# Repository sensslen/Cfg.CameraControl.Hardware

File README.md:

# Cfg.CameraControl.Hardware
Hardware needed to control a lanc camera with a PTZ head

The schematic looks like: 

## additional info
https://github.com/egnor/wt32-eth01

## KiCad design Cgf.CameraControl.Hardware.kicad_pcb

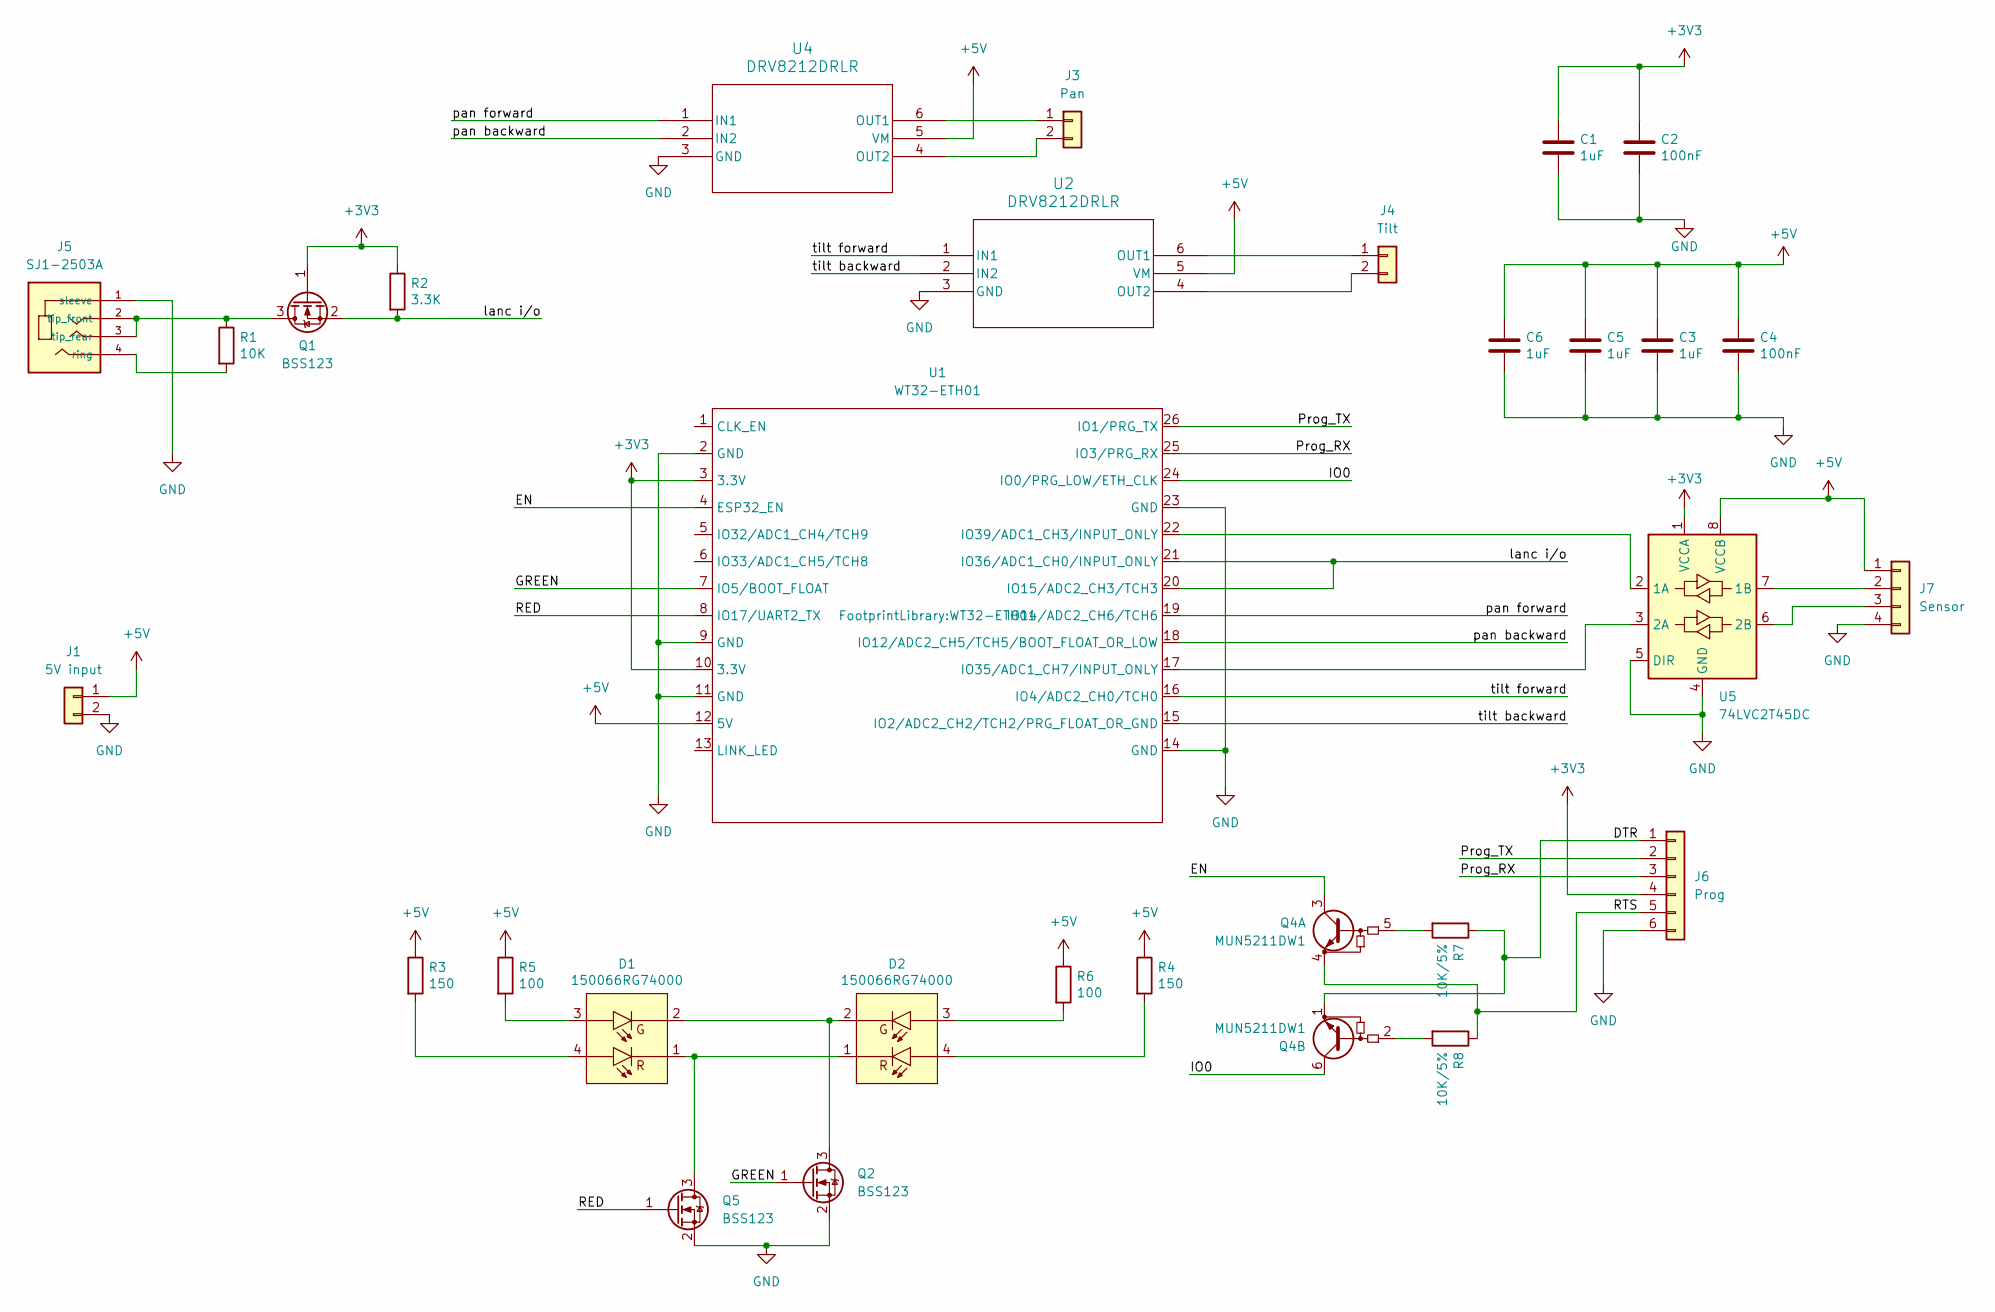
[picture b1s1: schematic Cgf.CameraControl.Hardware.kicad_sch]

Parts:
C1, C3, C5, C6: 1uF; C_0805_2012Metric
C2, C4: 100nF; C_0805_2012Metric
D1, D2: 150066RG74000; SMT_RG74000_WRE
J1: 5V input; PinHeader_1x02_P2.54mm_Vertical
J3: Pan; PinHeader_1x02_P2.54mm_Vertical
J4: Tilt; PinHeader_1x02_P2.54mm_Vertical
J5: SJ1-2503A; CUI_SJ1-2503A
J6: Prog; PinHeader_1x06_P2.54mm_Vertical
J7: Sensor; PinHeader_1x04_P2.54mm_Vertical
Q1, Q2, Q5: BSS123; SOT-23
Q4: MUN5211DW1; SOT-363_SC-70-6
R1: 10K; R_0805_2012Metric
R2: 3.3K; R_0805_2012Metric
R3, R4: 150; R_0805_2012Metric
R5, R6: 100; R_0805_2012Metric
R7, R8: 10K/5%; R_0805_2012Metric
U1: WT32-ETH01
U2, U4: DRV8212DRLR; SOT6_DRV8212_TEX
U5: 74LVC2T45DC; VSSOP8_74LVC2T45DC_125_NEX-L

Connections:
+3V3: C1.1, C2.1, J6.4, Q1.1 (G), R2.1, U1.3 (3.3V), U1.10 (3.3V), U5.1 (VCCA)
+5V: C3.1, C4.1, C5.1, C6.1, J1.1, J7.1, R3.1, R4.1, R5.1, R6.1, U1.12 (5V), U2.5 (VM), U4.5 (VM), U5.8 (VCCB)
/DTR: J6.1, Q4.1 (E2), R7.1
/EN: Q4.3 (C1), U1.4 (ESP32_EN)
/GREEN: Q2.1 (G), U1.7 (IO5/BOOT_FLOAT)
/IO0: Q4.6 (C2), U1.24 (IO0/PRG_LOW/ETH_CLK)
/Prog_RX: J6.3, U1.25 (IO3/PRG_RX)
/Prog_TX: J6.2, U1.26 (IO1/PRG_TX)
/RED: Q5.1 (G), U1.8 (IO17/UART2_TX)
/RTS: J6.5, Q4.4 (E1), R8.1
/lanc i/o: Q1.2 (S), R2.2, U1.20 (IO15/ADC2_CH3/TCH3), U1.21 (IO36/ADC1_CH0/INPUT_ONLY)
/pan backward: U1.18 (IO12/ADC2_CH5/TCH5/BOOT_FLOAT_OR_LOW), U4.2 (IN2)
/pan forward: U1.19 (IO14/ADC2_CH6/TCH6), U4.1 (IN1)
/tilt backward: U1.15 (IO2/ADC2_CH2/TCH2/PRG_FLOAT_OR_GND), U2.2 (IN2)
/tilt forward: U1.16 (IO4/ADC2_CH0/TCH0), U2.1 (IN1)
GND: C1.2, C2.2, C3.2, C4.2, C5.2, C6.2, J1.2, J5.1 (sleeve), J6.6, J7.4, Q2.2 (S), Q5.2 (S), U1.2 (GND), U1.9 (GND), U1.11 (GND), U1.14 (GND), U1.23 (GND), U2.3 (GND), U4.3 (GND), U5.4 (GND), U5.5 (DIR)
unnamed: D1.3, R5.2
unnamed: D1.4, R3.2
unnamed: D2.3, R6.2
unnamed: D2.4, R4.2
unnamed: J3.1, U4.6 (OUT1)
unnamed: J3.2, U4.4 (OUT2)
unnamed: J4.1, U2.6 (OUT1)
unnamed: J4.2, U2.4 (OUT2)
unnamed: J5.4 (ring), R1.2
unnamed: J5.2 (tip_front), J5.3 (tip_rear), Q1.3 (D), R1.1
unnamed: J7.2, U5.7 (1B)
unnamed: J7.3, U5.6 (2B)
unnamed: D1.2, D2.2, Q2.3 (D)
unnamed: Q4.5 (B1), R7.2
unnamed: Q4.2 (B2), R8.2
unnamed: D1.1, D2.1, Q5.3 (D)
unnamed: U1.17 (IO35/ADC1_CH7/INPUT_ONLY), U5.3 (2A)
unnamed: U1.22 (IO39/ADC1_CH3/INPUT_ONLY), U5.2 (1A)

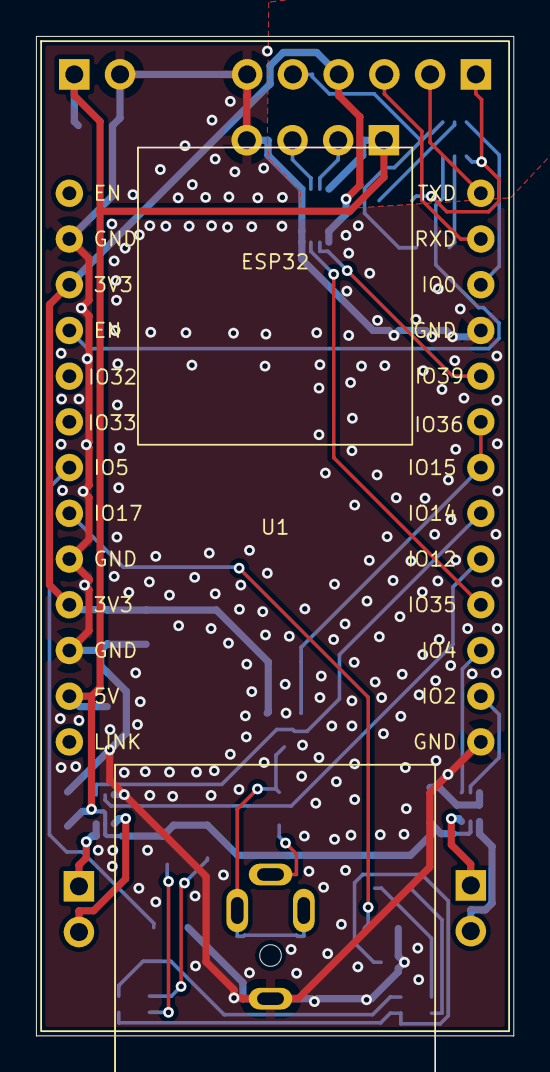
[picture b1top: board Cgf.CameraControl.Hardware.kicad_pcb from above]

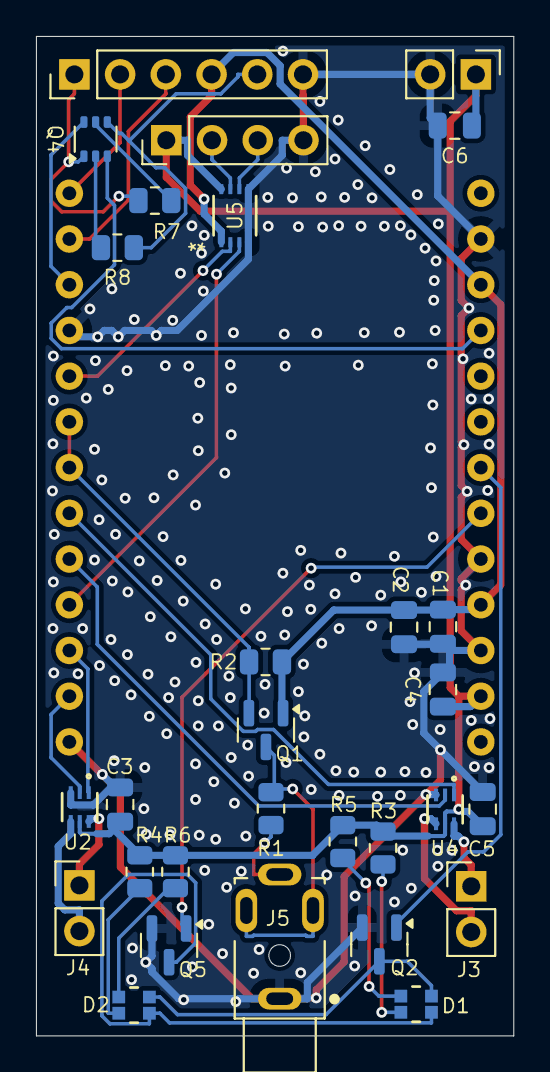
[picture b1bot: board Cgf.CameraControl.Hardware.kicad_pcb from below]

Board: 2 copper layers, 26.5 x 55.5 mm, 30 parts (29 on the bottom side), 34 nets.

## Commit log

2024-05-26 initial version
2024-05-26 use svg to show schematic
2024-05-26 include svg in description
2024-05-26 add background to schematic
2024-05-26 correctly add background
2024-05-28 make sure all parts have footprints and also simplify led circuit
2024-06-05 update schematic with suggestions
2024-06-09 Add additional info section to readme
2024-06-11 Apply suggestions from review
2024-06-15 Initial pcb layout
2024-06-15 replace footprint after the pcb failed validation
2024-06-15 improve layout
2024-06-15 Fix all design rules
2024-06-15 improve pcb
2026-01-05 aff pipeline to update license year
2026-01-05 Update copyright year in LICENSE file
